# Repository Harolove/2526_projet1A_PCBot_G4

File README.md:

# 2526_projet1A_PCBot_G4
PCBot fait par le groupe de 4

## Rappels git

### Clé SSH

Dans git bash, lancez la commande suivante :

```bash
ssh-keygen
```

puis affichez la clé :

```bash
cat /c/Users/<USER>/.ssh/id_ed25519.pub
```

Créez une nouvelle clé dans github et collez la clé

### Clonez le projet

Pour récupérer le projet, à faire une fois (par projet).

```bash
git clone git@github.com:Harolove/2526_projet1A_PCBot_G4.git
```

### Faire un commit

A faire à chaque fois que quelque chose fonctionne, et après une séance de travail.

```bash
git status
git add .
git commit -m "Message"
git push
```

### Récupérer la dernière version

A faire à chaque fois qu'on commence à travailler

```bash
git pull
```
## Timeline
### 05/02/2026
Début du projet : Le professeur nous présente différents projets.
Nous avons choisi le PCBot car le projet nous paraît très intéressant même s'il en est un gros. Nous avons également utilisé cette séance pour découvrir git et github. Nous avons commencé les recherches des datasheets des différents composants du PCBot; et nous avons listé les différentes fonctionnalités de celui-ci.

### 12/02/2026
Draw.io :
- Schéma architectural

Kicad : 
- Début du schematic
- Modification des symboles déjà existants sur Kicad pour avoir des composants qui se rapprochent de ceux que nous allons utiliser

### 19/02/2026
Kicad :
- Création des feuilles hiérarchiques
- Continuation du schematic sur Kicad

### 12/03/2026
Kicad :
- Continuation du schematic sur Kicad

### 19/03/2026
Kicad : 
- Ajout de connexions inter-feuille
CubeIDE : 
- Début de code (détermination de position, calcul de distance avec obstacle, déplacement dans l'espace)

### 25/03/2026
Kicad :
- Début du routage (ajout des Mounting_Hole_Pad)
- Ajout des plans de masse (GND pour couches n°1, 2 et 4)

### 26/03/2026
CubeIDE :
- Modification du code et ajout de code test (car nous n'avons pas encore la carte)

### 09/04/2026
CubeIDE :
- Correction d'erreurs

### 16/04/2026
CubeIDE :
- Commentaire des différents fichiers .c et .h
- Recherche d'une librairie pour le capteur TOF

### 06/05/2026
Software : 
- Réussite à faire communiquer deux nRF24 avec deux Nucléos-L476RG

### 07/05/2026
Pratique :
- Soudure du PCB
Software :
- Test du code pour la centrale inertielle

### 13/05/2026
Pratique :
- Resoudure du PCB (car nous avons eu des problèmes la première fois)

### 15/05/2026
Software :
- Fonctionnement de la centrale inertielle

### 18/05/2026
Software :
- Test du code pour le capteur tof (mais n'a pas réussi à le faire fonctionner)
Onshape :
- Modélisation d'un support pour le PCB

### 19/05/2026
Onshape :
- Impression et assemblage du support

### Introduction:

Ce projet a pour objectif la conception d'un robot PCBot capable de connaître sa position dans l'espace et de se déplacer de manière autonome. Ce robot doit pouvoir cartographier un environnement en mesurant la distance qui le sépare des obstacles, et en communiquant avec d'autres PCBot, il peut reconstruire la carte d'un environnement beaucoup plus large.

### Choix des composants:

Nous avons choisi nos composants par rapport à trois critères: l'écologie, l'optimisation de l'espace et le coût.
- Pour la gestion de l'énergie, nous avons retenu le BMS BQ25896RTWR, qui accepte une large plage de tension d'entrée (3,9V à 14V) et offre un rendement supérieur à 90% à 3A, permettant l'utilisation d'adaptateurs standards (5V) ou haute tension (9V/12V).
- Pour le contrôle des moteurs DFR1224 à courant continu, nous avons opté pour le driver DRV8411APWPR pour sa compacité et sa simplicité d'utilisation, avec une large plage de fonctionnement de 1.65V à 11V.
- La localisation du robot repose sur la centrale inertielle LSM6DSOX, qui possède un accéléromètre et un gyroscope (que l'on n'utilisera pas dans le projet) dans un boîtier résistant aux chocs mécaniques.
- Pour la mesure de distance, nous avons choisi le capteur TOF VL53L0X pour ses bonnes performances en pleine lumière dans un encombrement réduit. 
- La communication sans fil entre robots est assurée par le module nRF24.

### Routage et conception du PCB:

Pour le routage, nous avons cherché à minimiser les distances entre composants interdépendants, en plaçant notamment les condensateurs de découplage au plus près des composants qu'ils protègent. Le PCB a été optimisé pour atteindre une taille minimale de 5,9 × 6,8 cm pour l'écologie.
Exemple: 

###

### Difficultés rencontrées:
Le soudage des composants a été l'étape la plus délicate du projet, marquée par plusieurs tentatives avant d'obtenir un résultat satisfaisant. Notre premier PCB a été un échec, car après le passage au four, nous avons remarqué que nous n’avons pas retiré la pâte à braser au niveau des trous du connecteur USB-C, rendant ainsi la carte inutilisable. Lors du deuxième essai, de la pâte à braser s’est retirée par inadvertance à certains endroits, compromettant là encore la qualité des soudures.
Sur notre PCB final, le passage au four a provoqué le déplacement de notre BMS et de certains condensateurs. De plus, une patte de la STM32 s’est pliée rompant ainsi le contact électrique avec plusieurs broches du microcontrôleur. Pour corriger ces problèmes, nous avons dû dessouder les composants concernés et les ressouder manuellement à l'air chaud avec du flux un liquide qui permet à l'étain de couler jusqu'aux pattes lors du chauffage à l'air chaud. Malgré ces difficultés, cette expérience nous a appris énormément sur les contraintes du soudage en production et sur les techniques de reprise manuelle. 

Après le soudage, nous avons tenté d'alimenter le PCB via un chargeur USB-C, mais les tensions mesurées au multimètre ne correspondaient pas aux valeurs attendues. Nous avons découvert que deux solder jumpers, JP1 et JP2, étaient ouverts par défaut, nous avons donc dû poser de l'étain dessus pour enfin avoir des alimentations correctes. Nous avons également constaté que le PCB ne fonctionnait qu'avec un chargeur USB-A, le chargeur USB-C ne semblant pas être reconnu correctement, sans que nous ayons pu en identifier la cause précise.

Du côté logiciel, nous n'avons pas réussi à établir la communication I2C avec le capteur TOF, que ce soit sur le PCB du projet ou avec notre STM32L476RG. Pourtant, la broche XSHUT a bien été mise à 1 dans le code, et l'alimentation du composant a été vérifiée avec un multimètre. 

### Modélisation 3D du support:
Nous avons conçu le support du robot sur OnShape. La principale contrainte de conception était d'assurer que les deux roues arrière et la bille aient la même hauteur pour garantir une surface de contact plane. Nous avons donc ajouté de la matière à l'avant du support afin de compenser la différence de hauteur.
Nous avons fait différents trous pour pouvoir faire rentrer les vis des moteurs et de la bille, et nous avons aussi fait le support pour le PCB. Cependant, l'impression n'a pas été parfaite et le support ne s'est pas emboîté correctement, pour pallier le problème, nous avons cassé l'un des picots du support afin que le PCB puisse tenir en place.

### IMU
Dans le cadre du projet, nous avons réalisé quelques tests avec le composant LSM6DSOX (Adafruit 4438), notre objectif était de pouvoir obtenir la distance parcourue par le composant à partir des données accélérométriques (par double intégration). Nous avons relié les lignes SDA et SCL de l’imu sur les broches PB6 et PB7 du microcontrôleur STM32L476RG.
Avant de faire ces tests, nous avons utilisé le registre WHO_AM_I du composant d’adresse 0x0F et qui contient 0x6C (108). Après lecture du contenu à cette adresse nous avons obtenu cette valeur, cela montre que le capteur est bien connecté.
Les registres OUTX et OUTY permettent de mesurer l'accélération selon l’axe x et l’axe y, cependant, dans le cadre de ces tests, nous allons plutôt nous concentrer sur un seul axe.
L'accélération est codée sur 16 bits au total, mais le bus I2C ne peut transférer que 8 bits à la fois. Donc le capteur découpe la valeur en deux morceaux de 8 bits et les range dans deux registres séparés :
- OUTX_L_A (0x28) contient les 8 bits de poids faible
- OUTX_H_A (0x29) contient les 8 bits de poids fort.

Le registre CTRL1_XL d’adresse 0x10 est le registre de configuration principal de l'accéléromètre. Il est composé de 8 bits répartis en trois parties :
- Les 4 bits de poids fort (ODR_XL3 à ODR_XL0) règlent la fréquence de mesure
- Les 2 bits suivants (FS1_XL, FS0_XL) règlent la plage de mesure
- Le bit LPF2_XL_EN active ou non un filtre passe-bas

Pour nos tests nous avons choisi d’envoyer 0x40 à ce registre qui correspond en binaire à 0100 0000, on a donc :
- 0100 pour ODR_XL qui correspond à 104 Hz dans le tableau pour un mode normal
- 00 pour FS_XL qui correspond à la plage ±2g (valeur par défaut)
- 00 pour le reste: filtre désactivé

On fixe la fréquence d'échantillonnage du capteur à 104 Hz, ce qui signifie qu'il prend 104 mesures par seconde, ce qui est largement suffisant pour nos tests, puisque dt = 0.02s correspond à une fréquence de 50 Hz dans le code. Le capteur mesure donc deux fois plus vite que notre boucle de calcul.
On fixe la plage à ±2g qui est adaptée pour nos tests car nos déplacements sont lents et à faible accélération.

L'approche que nous avons opté pour le code est d’implanter plusieurs variables volatiles:

- measurement_active: cette variable vaut 1 si la mesure est active et 0 sinon.
- pos_x: la position de x actuelle.
- x_pos_max: la position maximale de pox_x pendant une mesure, elle a été introduite car pos_x varie en continu et ne permet pas de lire directement une valeur stable.
  
Une mesure est lancée dès que l’on appuie sur le bouton poussoir PC13 et s’arrête lorsqu’on réappuie dessus pour nous donner la valeur de x_pos_max au cours de cette mesure. 

L'estimation de la position repose sur une double intégration temporelle. Cependant, cette intégration pose un problème de précision, de petites erreurs s'accumulent à chaque intégration et fausse le calcul de la position même quand le robot est immobile. Ainsi, pour limiter ces erreurs, nous avons mis en place 2 corrections:
- Les valeurs brutes du capteur sont converties en m/s² selon la plage de mesure ±2g.
- Si l'accélération est inférieure à 0,20 m/s², on la considère comme du bruit et on l'ignore.

Après implémentation de ce code, nous avons lancé le débogueur et regardé les valeurs de pos_x, x_pos_max et measurement_active dans Live Expressions de l'IDE, permettant d'observer en temps réel ces variables. 
Pour vérifier si notre code fonctionne, nous avons choisi de faire déplacer le capteur de 10 cm, après plusieurs essais, nous obtenons des résultats entre 9.1 et 10.5 cm, ce qui est plutôt satisfaisant.

Voici ce qu'on observe :

### nRF24:

Pour ce projet, nous avons besoin de faire communiquer deux robots distants.
Les capteurs LiDAR permettent une mesure précise, mais leur coût élevé et leur complexité de mise en œuvre (drivers, protocoles temps réel) dépassent les contraintes du projet. Nous avons donc opté pour une communication radio bas-coût avec le module nRF24L01+, qui offre une liaison sans fil simple à intégrer via SPI et suffisamment fiable pour nos besoins.
Nous avons relié deux modules nRF24L01+ à deux cartes Nucleo-L476RG et vérifié que les deux microcontrôleurs pouvaient s'échanger des messages de manière bidirectionnelle :

## Connexion matérielle:
Le nRF24L01+ communique via le bus SPI. Voici le câblage utilisé sur le STM32L476RG :
-	CE → PA8 (contrôle émission/réception)
-	CSN → PB6 (Chip Select SPI)
-	SCK → PA5 (SPI1_SCK)
-	MOSI → PA7 (SPI1_MOSI)
-	MISO → PA6 (SPI1_MISO)
-	VCC → 3.3 V  |  GND → GND

## Configuration du module:
Les principaux paramètres configurés dans nos tests :
-	Canal RF : canal 76, libre des perturbations Wi-Fi les plus courantes.
-	Débit : 1 Mbps — bon compromis portée/fiabilité pour notre usage.
-	Puissance d'émission : 0 dBm (niveau max), pour assurer la fiabilité en intérieur.
-	Taille de payload : 32 octets (mode statique).
-	Adresses : une adresse TX et une adresse RX configurées de façon symétrique sur les deux cartes.

La validation de la connexion SPI a été réalisée en lisant le registre CONFIG (adresse 0x00) : si la valeur retournée est cohérente (typiquement 0x08 après reset), le module est bien connecté et répond correctement.

## Approche logicielle:
Nous avons distingué deux rôles : un émetteur (TX) et un récepteur (RX), chacun configuré sur une Nucleo. Les fonctions principales sont :
-	nrf24_init() : initialise le SPI et configure les registres (canal, débit, adresses, taille payload).
-	nrf24_send(data, len) : place le module en mode TX, envoie le payload, attend l'acquittement (Auto-ACK).
-	nrf24_receive(buf) : place le module en mode RX, poll le registre STATUS pour détecter une donnée disponible, puis lit le FIFO.

Le bouton poussoir PC13 de la carte émettrice déclenche l'envoi d'un message. La carte réceptrice allume une LED (PA5) à chaque réception confirmée, permettant une vérification visuelle sans débogueur.

## Résultats:
Les tests montrent une communication stable entre les deux cartes.

### Conclusion:
À la fin du projet, nous avons réussi à faire communiquer deux nRF24 entre eux, la centrale inertielle a part et à faire fonctionner les 2 moteurs de roue, donc le robot peut se déplacer mais il ne peut pas encore s'arrêter librement ni changer de vitesse; les 2 LEDs fonctionnent, si D1 celà signifie que le PCB est alimenté et si D2 clignote c'est qu'il y a une erreur au niveau de la batterie (qui n'est pas connectée).

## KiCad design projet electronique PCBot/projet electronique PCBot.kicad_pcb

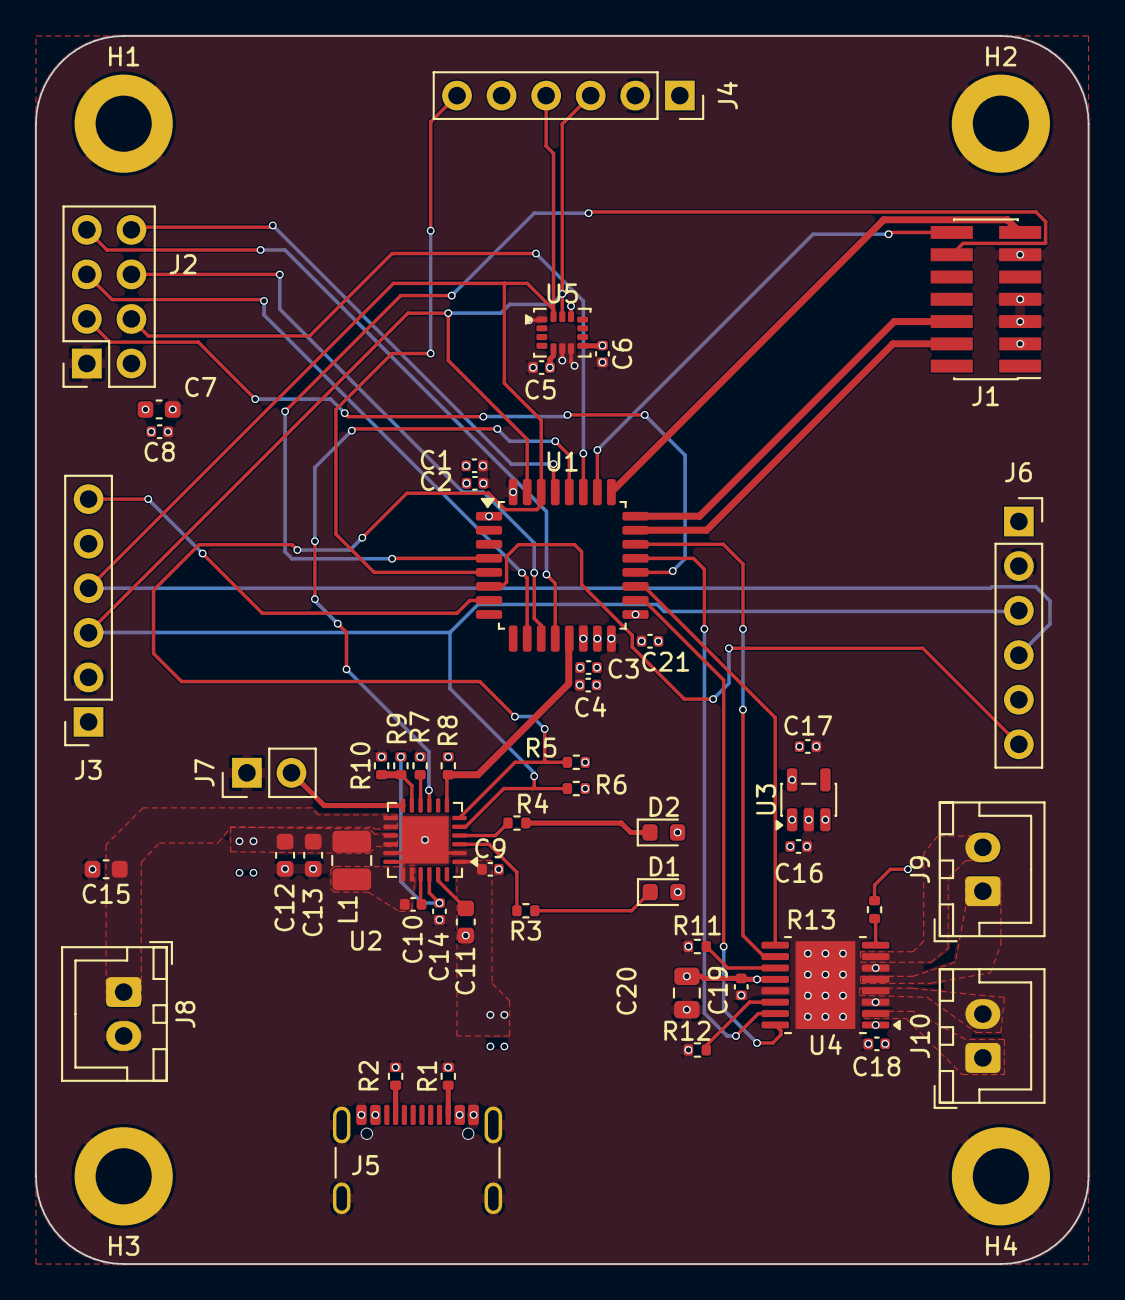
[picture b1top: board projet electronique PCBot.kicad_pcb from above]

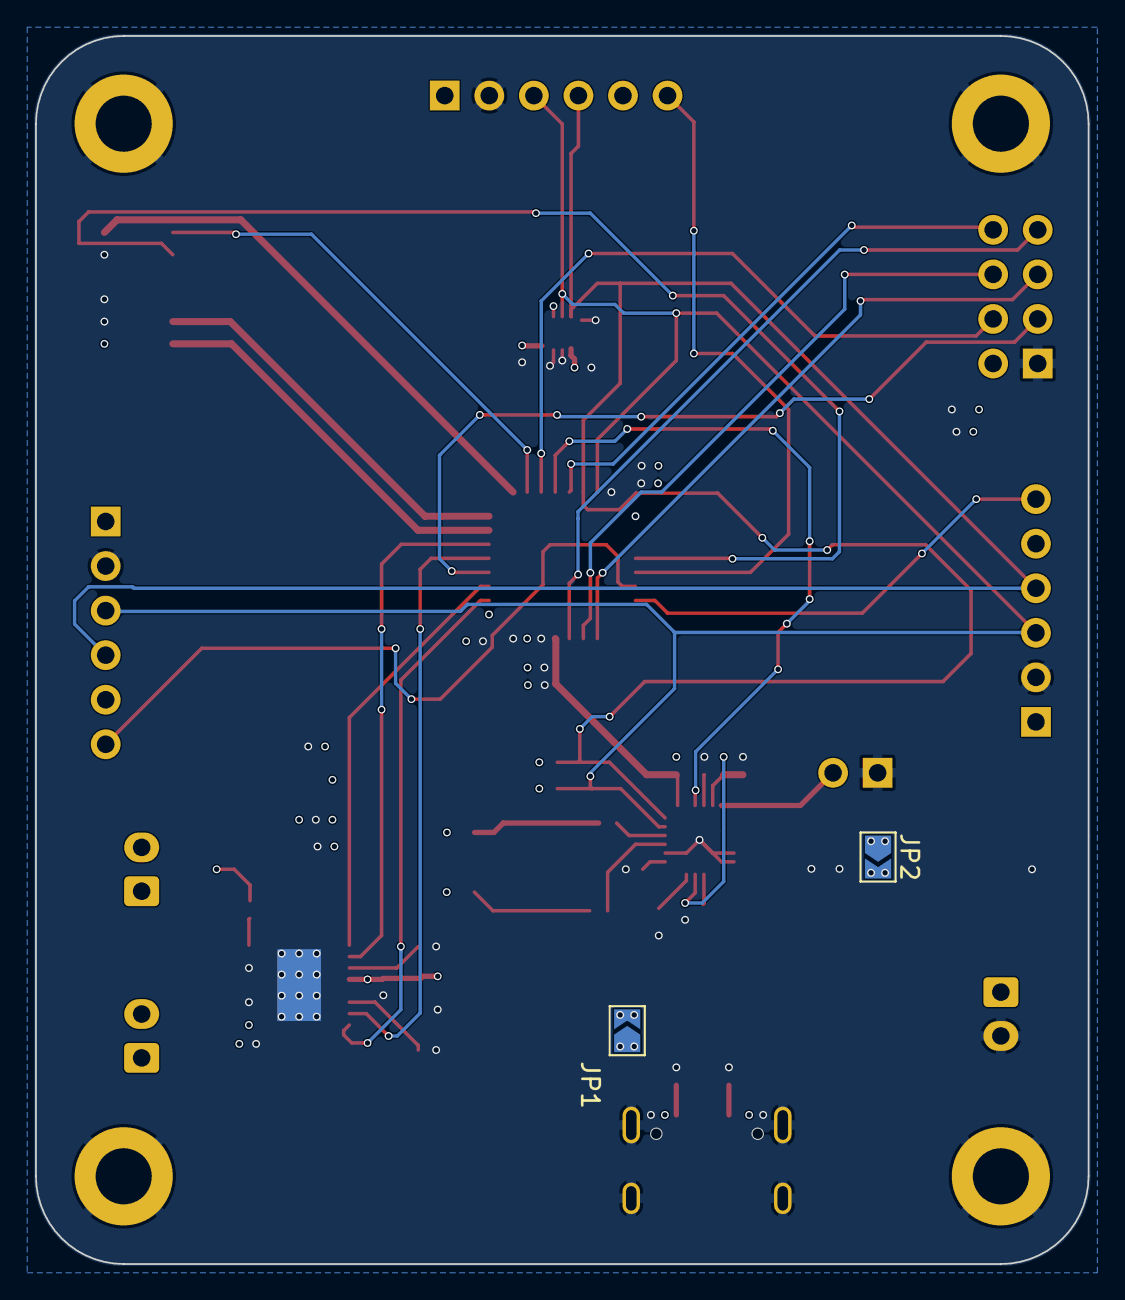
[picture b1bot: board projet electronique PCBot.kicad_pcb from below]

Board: 4 copper layers, 60.0 x 70.0 mm, 58 parts (2 on the bottom side), 49 nets.

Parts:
C1: 4.7u; C_0402_1005Metric
C2, C5, C6, C8, C18, C19, C21: 100n; C_0402_1005Metric
C3: 10n; C_0402_1005Metric
C4, C9, C16, C17: 1u; C_0402_1005Metric
C7, C12, C13, C15: 10u; C_0603_1608Metric
C10: 47n; C_0402_1005Metric
C11: 8u2; C_0603_1608Metric
C14: 4u7; C_0402_1005Metric
C20: 47u; C_0805_2012Metric
D1, D2: LED; LED_0603_1608Metric
H1, H2, H3, H4: MountingHole_Pad; MountingHole_3.2mm_M3_DIN965_Pad
J1: Conn_ST_STDC14; PinHeader_2x07_P1.27mm_Vertical_SMD
J2: nRF24; PinSocket_2x04_P2.54mm_Vertical
J3, J4, J6: TOF; PinSocket_1x06_P2.54mm_Vertical
J5: USB_C_Receptacle_USB2.0_16P; USB_C_Receptacle_GCT_USB4105-xx-A_16P_TopMnt_Horizontal
J7: ON SWITCH; PinHeader_1x02_P2.54mm_Vertical
J8, J9, J10: Conn_01x02_Pin; JST_XH_B2B-XH-A_1x02_P2.50mm_Vertical
JP1, JP2: SolderJumper_2_Open; SolderJumper-2_P1.3mm_Open_TrianglePad1.0x1.5mm
L1: 1u; L_1008_2520Metric
R1, R2: 5k1; R_0402_1005Metric
R3, R4: 1k; R_0402_1005Metric
R5, R6, R8, R9, R10, R11, R12, R13: 10k; R_0402_1005Metric
R7: 270R; R_0402_1005Metric
U1: STM32G431KBT6; LQFP-32_7x7mm_P0.8mm
U2: BQ25896RTWR; Texas_RTW_WQFN-24-1EP_4x4mm_P0.5mm_EP2.7x2.7mm
U3: BU33SD5WG-TR; SOT-23-5
U4: DRV8411APWPR; HTSSOP-16-1EP_4.4x5mm_P0.65mm_EP3.4x5mm_Mask2.46x2.31mm_The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
U5: LSM6DSOX; LGA-14_3x2.5mm_P0.5mm_LayoutBorder3x4y

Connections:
+3.3V: C1.1, C2.1, C3.1, C4.1, C5.2, C6.1, C7.1, C8.1, C17.1, C18.2, C21.1, J1.3 (VCC), J2.2, J3.1 (3.3V), J4.1 (3.3V), J6.1 (3.3V), R5.1, R6.1, R8.1, R13.1, U1.1 (VDD), U1.15 (VDDA), U1.17 (VDD), U3.5 (VOUT), U4.1 (VREF), U5.5 (VDDIO), U5.8 (VDD), U5.12 (CS)
/Capteur/CE: J2.3, U1.20 (PA10)
/Capteur/CSN: J2.4, U1.27 (PB4)
/Capteur/IRQ: J2.8, U1.29 (PB6)
/Capteur/MISO: J2.7, U1.12 (PA7)
/Capteur/MOSI: J2.6, U1.11 (PA6)
/Capteur/SCK: J2.5, U1.10 (PA5)
/Capteur/SCL: J3.3 (SCL), J4.3 (SCL), J6.3 (SCL), R6.2, U1.31 (PB8), U2.5 (SCL), U5.13 (SCL)
/Capteur/SDA: J3.4 (SDA), J4.4 (SDA), J6.4 (SDA), R5.2, U1.30 (PB7), U2.6 (SDA), U5.14 (SDA)
/Capteur/TOF1_XSHUT: J3.6 (XST), U1.7 (PA2)
/Capteur/TOF2_XSHUT: J6.6 (XST), U1.6 (PA1)
/Capteur/TOF3_XSHUT: J4.6 (XST), U1.5 (PA0)
/Driver/AOUT1: J10.1, U4.2 (AOUT1)
/Driver/AOUT2: J10.2, U4.4 (AOUT2)
/Driver/BOUT1: J9.2, U4.7 (BOUT1)
/Driver/BOUT2: J9.1, U4.5 (BOUT2)
/Driver/TIM1_CH1: U1.18 (PA8), U4.16 (AIN1)
/Driver/TIM1_CH1N: U1.21 (PA11), U4.15 (AIN2)
/Driver/TIM1_CH2: U1.19 (PA9), U4.9 (BIN1)
/Driver/TIM1_CH2N: U1.22 (PA12), U4.10 (BIN2)
/Driver/nFAULT: R13.2, U4.8 (nFAULT)
/Gestion d'energie/INT: R8.2, U1.13 (PB0), U2.7 (INT)
/Gestion d'energie/SW: C10.1, L1.1, U2.19 (SW), U2.20 (SW)
/Gestion d'energie/SYS: C16.1, C19.1, C20.1, D1.2 (A), D2.2 (A), JP2.2 (B), U3.1 (VIN), U3.3 (~SHDN), U4.12 (VM)
/Gestion d'energie/VBUS: J5.A4 (VBUS), J5.A9 (VBUS), J5.B4 (VBUS), J5.B9 (VBUS), JP1.1 (A)
/Gestion d'energie/VBUS_TO_BQ: C9.1, JP1.2 (B), U2.1 (VBUS)
/Gestion d'energie/~CE: U1.28 (PB5), U2.9 (~CE)
/STM32/NRST: J1.12 (~RST), U1.4 (PG10)
/STM32/SYS_JTCK-SWCLK: J1.6 (JCLK/SWCLK), U1.24 (PA14)
/STM32/SYS_JTMS-SWDIO: J1.4 (JTMS/SWDIO), U1.23 (PA13)
/STM32/USART2_RX: J1.13 (VCP_RX), U1.25 (PA15)
/STM32/USART2_TX: J1.14 (VCP_TX), U1.26 (PB3)
GND: C1.2, C2.2, C3.2, C4.2, C5.1, C6.2, C7.2, C8.2, C9.2, C11.1, C12.2, C13.2, C14.2, C15.2, C16.2, C17.2, C18.1, C19.2, C20.2, C21.2, H1.1 (1_1), H2.1 (1_1), H3.1 (1_1), H4.1 (1_1), J1.5 (GND), J1.7 (GND), J1.11 (GNDDetect), J2.1, J3.2 (GND), J4.2 (GND), J5.A1 (GND), J5.A12 (GND), J5.B1 (GND), J5.B12 (GND), J5.S1 (SHIELD), J6.2 (GND), J7.1, J8.2, R1.2, R2.2, R7.1, R10.2, R11.1, R12.1, U1.14 (VSSA), U1.16 (VSS), U1.32 (VSS), U2.2 (PSEL), U2.17 (PGND), U2.18 (PGND), U2.25 (PGND), U3.2 (GND), U4.3 (PGNDA), U4.6 (PGNDB), U4.13 (GND), U4.17 (GND(PPAD)), U5.1 (SDO/SA0), U5.6 (GND), U5.7 (GND)
unnamed: D1.1 (K), R3.1
unnamed: D2.1 (K), R4.2
unnamed: J5.A5 (CC1), R2.1
unnamed: J5.B5 (CC2), R1.1
unnamed: J7.2, U2.12 (~QON)
unnamed: C15.1, J8.1, U2.13 (BAT), U2.14 (BAT)
unnamed: C12.1, C13.1, JP2.1 (A), L1.2, U2.15 (SYS), U2.16 (SYS)
unnamed: C10.2, U2.21 (BTST)
unnamed: R7.2, U2.10 (ILIM)
unnamed: C11.2, U2.23 (PMID)
unnamed: C14.1, R9.1, U2.22 (REGN)
unnamed: R4.1, U2.4 (STAT)
unnamed: R9.2, R10.1, U2.11 (TS)
unnamed: R3.2, U2.3 (~PG)
unnamed: R12.2, U4.14 (AIPROPI)
unnamed: R11.2, U4.11 (BIPROPI)

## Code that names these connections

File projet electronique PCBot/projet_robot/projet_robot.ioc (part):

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Mcu.Name=STM32G431K(6-8-B)Tx
Mcu.Package=LQFP32
Mcu.UserName=STM32G431KBTx
PA0.GPIOParameters=GPIO_Label
PA0.GPIO_Label=TOF3_XSHUT
PA0.Signal=GPIO_Output
PA1.GPIOParameters=GPIO_Label
PA1.GPIO_Label=TOF2_XSHUT
PA1.Signal=GPIO_Output
PA11.Mode=PWM Generation1 CH1 CH1N
PA11.Signal=TIM1_CH1N
PA12.Mode=Output Compare2 CH2 CH2N
PA12.Signal=TIM1_CH2N
PA13.Mode=Serial_Wire
PA13.Signal=SYS_JTMS-SWDIO
PA14.Mode=Serial_Wire
PA14.Signal=SYS_JTCK-SWCLK
PA15.Mode=Asynchronous
PA15.Signal=USART2_RX
PA2.GPIOParameters=GPIO_Label
PA2.GPIO_Label=TOF1_XSHUT
PA2.Signal=GPIO_Output
PA5.Signal=SPI1_SCK
PA8.Signal=S_TIM1_CH1
PA9.Signal=S_TIM1_CH2
PB0.Signal=GPXTI0
PB3.Mode=Asynchronous
PB3.Signal=USART2_TX
PB5.Signal=GPIO_Output
PB7.Mode=I2C
PB7.Signal=I2C1_SDA
PB8-BOOT0.Mode=I2C
PB8-BOOT0.Signal=I2C1_SCL
RCC.HSE_VALUE=8000000
RCC.SYSCLKFreq_VALUE=16000000
board=custom

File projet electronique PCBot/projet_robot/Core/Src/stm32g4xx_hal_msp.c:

/* USER CODE BEGIN Header */
/**
  ******************************************************************************
  * @file         stm32g4xx_hal_msp.c
  * @brief        This file provides code for the MSP Initialization
  *               and de-Initialization codes.
  ******************************************************************************
  * @attention
  *
  * Copyright (c) 2026 STMicroelectronics.
  * All rights reserved.
  *
  * This software is licensed under terms that can be found in the LICENSE file
  * in the root directory of this software component.
  * If no LICENSE file comes with this software, it is provided AS-IS.
  *
  ******************************************************************************
  */
/* USER CODE END Header */

/* Includes ------------------------------------------------------------------*/
#include "main.h"
/* USER CODE BEGIN Includes */

/* USER CODE END Includes */

/* Private typedef -----------------------------------------------------------*/
/* USER CODE BEGIN TD */

/* USER CODE END TD */

/* Private define ------------------------------------------------------------*/
/* USER CODE BEGIN Define */

/* USER CODE END Define */

/* Private macro -------------------------------------------------------------*/
/* USER CODE BEGIN Macro */

/* USER CODE END Macro */

/* Private variables ---------------------------------------------------------*/
/* USER CODE BEGIN PV */

/* USER CODE END PV */

/* Private function prototypes -----------------------------------------------*/
/* USER CODE BEGIN PFP */

/* USER CODE END PFP */

/* External functions --------------------------------------------------------*/
/* USER CODE BEGIN ExternalFunctions */

/* USER CODE END ExternalFunctions */

/* USER CODE BEGIN 0 */

/* USER CODE END 0 */

void HAL_TIM_MspPostInit(TIM_HandleTypeDef *htim);
                    /**
  * Initializes the Global MSP.
  */
void HAL_MspInit(void)
{

  /* USER CODE BEGIN MspInit 0 */

  /* USER CODE END MspInit 0 */

  __HAL_RCC_SYSCFG_CLK_ENABLE();
  __HAL_RCC_PWR_CLK_ENABLE();

  /* System interrupt init*/

  /** Disable the internal Pull-Up in Dead Battery pins of UCPD peripheral
  */
  HAL_PWREx_DisableUCPDDeadBattery();

  /* USER CODE BEGIN MspInit 1 */

  /* USER CODE END MspInit 1 */
}

/**
  * @brief I2C MSP Initialization
  * This function configures the hardware resources used in this example
  * @param hi2c: I2C handle pointer
  * @retval None
  */
void HAL_I2C_MspInit(I2C_HandleTypeDef* hi2c)
{
  GPIO_InitTypeDef GPIO_InitStruct = {0};
  RCC_PeriphCLKInitTypeDef PeriphClkInit = {0};
  if(hi2c->Instance==I2C1)
  {
    /* USER CODE BEGIN I2C1_MspInit 0 */

    /* USER CODE END I2C1_MspInit 0 */

  /** Initializes the peripherals clocks
  */
    PeriphClkInit.PeriphClockSelection = RCC_PERIPHCLK_I2C1;
    PeriphClkInit.I2c1ClockSelection = RCC_I2C1CLKSOURCE_PCLK1;
    if (HAL_RCCEx_PeriphCLKConfig(&PeriphClkInit) != HAL_OK)
    {
      Error_Handler();
    }

    __HAL_RCC_GPIOB_CLK_ENABLE();
    /**I2C1 GPIO Configuration
    PB7     ------> I2C1_SDA
    PB8-BOOT0     ------> I2C1_SCL
    */
    GPIO_InitStruct.Pin = GPIO_PIN_7|GPIO_PIN_8;
    GPIO_InitStruct.Mode = GPIO_MODE_AF_OD;
    GPIO_InitStruct.Pull = GPIO_PULLUP;
    GPIO_InitStruct.Speed = GPIO_SPEED_FREQ_LOW;
    GPIO_InitStruct.Alternate = GPIO_AF4_I2C1;
    HAL_GPIO_Init(GPIOB, &GPIO_InitStruct);

    /* Peripheral clock enable */
    __HAL_RCC_I2C1_CLK_ENABLE();
    /* USER CODE BEGIN I2C1_MspInit 1 */

    /* USER CODE END I2C1_MspInit 1 */

  }

}

/**
  * @brief I2C MSP De-Initialization
  * This function freeze the hardware resources used in this example
  * @param hi2c: I2C handle pointer
  * @retval None
  */
void HAL_I2C_MspDeInit(I2C_HandleTypeDef* hi2c)
{
  if(hi2c->Instance==I2C1)
  {
    /* USER CODE BEGIN I2C1_MspDeInit 0 */

    /* USER CODE END I2C1_MspDeInit 0 */
    /* Peripheral clock disable */
    __HAL_RCC_I2C1_CLK_DISABLE();

    /**I2C1 GPIO Configuration
    PB7     ------> I2C1_SDA
    PB8-BOOT0     ------> I2C1_SCL
    */
    HAL_GPIO_DeInit(GPIOB, GPIO_PIN_7);

    HAL_GPIO_DeInit(GPIOB, GPIO_PIN_8);

    /* USER CODE BEGIN I2C1_MspDeInit 1 */

    /* USER CODE END I2C1_MspDeInit 1 */
  }

}

/**
  * @brief TIM_Base MSP Initialization
  * This function configures the hardware resources used in this example
  * @param htim_base: TIM_Base handle pointer
  * @retval None
  */
void HAL_TIM_Base_MspInit(TIM_HandleTypeDef* htim_base)
{
  if(htim_base->Instance==TIM1)
  {
    /* USER CODE BEGIN TIM1_MspInit 0 */

    /* USER CODE END TIM1_MspInit 0 */
    /* Peripheral clock enable */
    __HAL_RCC_TIM1_CLK_ENABLE();
    /* USER CODE BEGIN TIM1_MspInit 1 */

    /* USER CODE END TIM1_MspInit 1 */

  }

}

void HAL_TIM_MspPostInit(TIM_HandleTypeDef* htim)
{
  GPIO_InitTypeDef GPIO_InitStruct = {0};
  if(htim->Instance==TIM1)
  {
    /* USER CODE BEGIN TIM1_MspPostInit 0 */

    /* USER CODE END TIM1_MspPostInit 0 */

    __HAL_RCC_GPIOA_CLK_ENABLE();
    /**TIM1 GPIO Configuration
    PA8     ------> TIM1_CH1
    PA9     ------> TIM1_CH2
    PA11     ------> TIM1_CH1N
    PA12     ------> TIM1_CH2N
    */
    GPIO_InitStruct.Pin = GPIO_PIN_8|GPIO_PIN_9|GPIO_PIN_11|GPIO_PIN_12;
    GPIO_InitStruct.Mode = GPIO_MODE_AF_PP;
    GPIO_InitStruct.Pull = GPIO_NOPULL;
    GPIO_InitStruct.Speed = GPIO_SPEED_FREQ_LOW;
    GPIO_InitStruct.Alternate = GPIO_AF6_TIM1;
    HAL_GPIO_Init(GPIOA, &GPIO_InitStruct);

    /* USER CODE BEGIN TIM1_MspPostInit 1 */

    /* USER CODE END TIM1_MspPostInit 1 */
  }

}
/**
  * @brief TIM_Base MSP De-Initialization
  * This function freeze the hardware resources used in this example
  * @param htim_base: TIM_Base handle pointer
  * @retval None
  */
void HAL_TIM_Base_MspDeInit(TIM_HandleTypeDef* htim_base)
{
  if(htim_base->Instance==TIM1)
  {
    /* USER CODE BEGIN TIM1_MspDeInit 0 */

    /* USER CODE END TIM1_MspDeInit 0 */
    /* Peripheral clock disable */
    __HAL_RCC_TIM1_CLK_DISABLE();
    /* USER CODE BEGIN TIM1_MspDeInit 1 */

    /* USER CODE END TIM1_MspDeInit 1 */
  }

}

/**
  * @brief UART MSP Initialization
  * This function configures the hardware resources used in this example
  * @param huart: UART handle pointer
  * @retval None
  */
void HAL_UART_MspInit(UART_HandleTypeDef* huart)
{
  GPIO_InitTypeDef GPIO_InitStruct = {0};
  RCC_PeriphCLKInitTypeDef PeriphClkInit = {0};
  if(huart->Instance==USART2)
  {
    /* USER CODE BEGIN USART2_MspInit 0 */

    /* USER CODE END USART2_MspInit 0 */

  /** Initializes the peripherals clocks
  */
    PeriphClkInit.PeriphClockSelection = RCC_PERIPHCLK_USART2;
    PeriphClkInit.Usart2ClockSelection = RCC_USART2CLKSOURCE_PCLK1;
    if (HAL_RCCEx_PeriphCLKConfig(&PeriphClkInit) != HAL_OK)
    {
      Error_Handler();
    }

    /* Peripheral clock enable */
    __HAL_RCC_USART2_CLK_ENABLE();

    __HAL_RCC_GPIOA_CLK_ENABLE();
    __HAL_RCC_GPIOB_CLK_ENABLE();
    /**USART2 GPIO Configuration
    PA15     ------> USART2_RX
    PB3     ------> USART2_TX
    */
    GPIO_InitStruct.Pin = GPIO_PIN_15;
    GPIO_InitStruct.Mode = GPIO_MODE_AF_PP;
    GPIO_InitStruct.Pull = GPIO_NOPULL;
    GPIO_InitStruct.Speed = GPIO_SPEED_FREQ_LOW;
    GPIO_InitStruct.Alternate = GPIO_AF7_USART2;
    HAL_GPIO_Init(GPIOA, &GPIO_InitStruct);

    GPIO_InitStruct.Pin = GPIO_PIN_3;
    GPIO_InitStruct.Mode = GPIO_MODE_AF_PP;
    GPIO_InitStruct.Pull = GPIO_NOPULL;
    GPIO_InitStruct.Speed = GPIO_SPEED_FREQ_LOW;
    GPIO_InitStruct.Alternate = GPIO_AF7_USART2;
    HAL_GPIO_Init(GPIOB, &GPIO_InitStruct);

    /* USER CODE BEGIN USART2_MspInit 1 */

    /* USER CODE END USART2_MspInit 1 */

  }

}

/**
  * @brief UART MSP De-Initialization
  * This function freeze the hardware resources used in this example
  * @param huart: UART handle pointer
  * @retval None
  */
void HAL_UART_MspDeInit(UART_HandleTypeDef* huart)
{
  if(huart->Instance==USART2)
  {
    /* USER CODE BEGIN USART2_MspDeInit 0 */

    /* USER CODE END USART2_MspDeInit 0 */
    /* Peripheral clock disable */
    __HAL_RCC_USART2_CLK_DISABLE();

    /**USART2 GPIO Configuration
    PA15     ------> USART2_RX
    PB3     ------> USART2_TX
    */
    HAL_GPIO_DeInit(GPIOA, GPIO_PIN_15);

    HAL_GPIO_DeInit(GPIOB, GPIO_PIN_3);

    /* USER CODE BEGIN USART2_MspDeInit 1 */

    /* USER CODE END USART2_MspDeInit 1 */
  }

}

/* USER CODE BEGIN 1 */

/* USER CODE END 1 */

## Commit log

2026-02-05 Test de Dignon
2026-02-05 Test
2026-02-05 Update README with Git usage instructions
    Added Git reminders and commands for SSH key generation, cloning, committing, and pulling changes.
2026-02-05 Update README with reminder for next week
    Added a reminder to gather information before next week.
2026-02-12 Schematics
2026-02-18 De petites modifications
2026-02-18 Update README with project timeline and tasks
    Added project timeline and initial tasks to README.
2026-02-19 Ajout feuilles hiérarchiques
2026-02-19 Ajout de la feuille hiérarchique moteur
2026-02-19 Modification des feuilles hiérarchiques et le main
2026-02-19 ajout de la feuille connecteurs
2026-02-19 programme du 19/02/2026
2026-02-19 ajout de la feuille usb
2026-02-19 modification de la feuille driver
2026-02-19 Ajour USB
2026-02-19 modification gestion_energie
2026-03-12 feuille driver
2026-03-12 feuille driver 2
2026-03-12 modification de la feuille capteurs
2026-03-12 fichier driver et gestion d'energie
2026-03-12 modif
2026-03-12 stm32
2026-03-12 connec
2026-03-12 re modification de gestion energie
2026-03-18 modifications dans feuilles stm et capteurs
2026-03-19 modif de flo capteur
2026-03-19 modif de capteurs le vrai de vrai
2026-03-19 suppression feuilles moteurs et connecteurs + modif feuille stm
2026-03-19 suppr
2026-03-19 Ajout du projet STM32CubeIDE pour le robot
2026-03-19 ajout code v1
2026-03-19 ajout de connexions
2026-03-19 changement de capteur et moteur code
2026-03-19 modifs
2026-03-19 petites modifications
2026-03-23 modif un lundi lambda
2026-03-23 re modif de lundi
2026-03-24 grosse modif pcb du prof
2026-03-25 modif après revu prof
2026-03-25 début routage
2026-03-26 placement sur kicad debut
2026-03-26 modif code
2026-03-26 ajout de commentaires et nouveaux fichiers
2026-03-26 suite placement composants
2026-03-26 routage avec bcp d'erreurs
2026-03-26 suite routage
2026-03-26 routage avec 30 erreurs
2026-03-30 modif routage fin
2026-03-31 routageee
2026-04-02 Dernières corrections LFiack
2026-04-09 define
2026-04-09 ajout fichier
2026-04-09 modification README
2026-04-09 commentaires de code
2026-04-16 ajout commentaires
2026-04-16 stm fichier moteur
2026-04-16 modification main map moteur zone à la fin de l'heure
2026-04-16 modification odometrie.c
2026-05-07 début de modification du readme
2026-05-20 modifications code
2026-05-20 modification du readme
2026-05-20 nrf24 et imu
2026-05-20 modif stm pour le tof
2026-05-21 dernière modification du readme
2026-05-21 modification code nRF24
2026-05-21 README
2026-05-29 modification finale pour la centrale inertielle
2026-05-31 Update README.md
    final?
2026-05-31 Mes modifs sur le projet et le README
2026-05-31 Mise à jour finale du readme par Florence
2026-05-31 nettoyage
